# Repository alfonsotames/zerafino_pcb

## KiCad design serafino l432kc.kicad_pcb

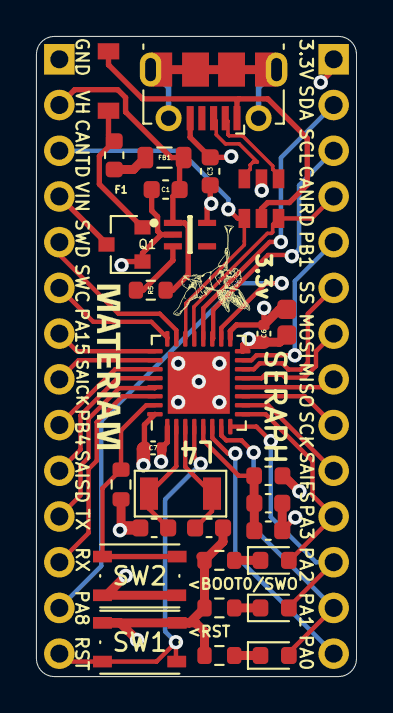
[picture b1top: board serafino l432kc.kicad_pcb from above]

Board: 4 copper layers, 17.8 x 35.6 mm, 31 parts (0 on the bottom side), 41 nets.

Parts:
C1, C10: 1uF; C_0603_1608Metric
C3: 2.2uF; C_0603_1608Metric
C4, C5: 4.3pF; C_0603_1608Metric
C6, C7: 100nF; C_0402_1005Metric
C8: 4.7uF; CP_EIA-1608-08_AVX-J
C9: 10nF; C_0603_1608Metric
D1: RED; LED_0603_1608Metric
D2: B5819W; D_SOD-123
D3: GREEN; LED_0603_1608Metric
D4: BLUE; LED_0603_1608Metric
F1: 200mA; Fuse_0603_1608Metric
FB1: 600@100MHz; L_0805_2012Metric
J1: USB_B_Micro; USB_Micro-B_Molex-105017-0001
J2, J3: Conn_01x14; PinHeader_1x14_P2.54mm_Vertical
L1: 600@100MHz; L_0603_1608Metric
Q1: SI3401A-TP; SOT-23
R1: 270; R_0603_1608Metric
R2: 10K; R_0603_1608Metric
R3: 1K; R_0603_1608Metric
R4: 330; R_0603_1608Metric
R5: 100k; R_0603_1608Metric
SW1, SW2: SW_Push; SW_Push_1P1T_NO_Vertical_Wuerth_434133025816
U1: STLQ020C33R; STMicroelectronics-ESDALC6V1W5-0
U2: USBLC6-2SC6; SOT-23-6
U3: STM32L432KCUx; QFN-32-1EP_5x5mm_P0.5mm_EP3.45x3.45mm
Y1: 32.768K; NX3215SA

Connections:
+3.3VA: C9.1, C10.1, L1.2, U3.5 (VDDA)
+3V3: C3.1, C6.1, C7.1, C8.1, J3.1, L1.1, SW2.2, U1.5 (VOUT), U3.1 (VDD), U3.17 (VDD)
+5V: D2.2 (A), J1.1 (VBUS), U2.5 (VBUS)
+VIN: J2.4, Q1.3 (D)
BOOT0: R2.2, SW2.1, U3.31 (PH3)
CAN_RD: J3.4, U2.6 (I/O1), U3.21 (PA11)
CAN_TD: J2.3, U2.4 (I/O2), U3.22 (PA12)
GND: C1.2, C3.2, C4.2, C5.2, C6.2, C7.2, C8.2, C9.2, C10.2, J1.5 (GND), J2.1, Q1.1 (G), R1.2, R2.1, R3.2, R4.2, SW1.1, U1.2 (GND), U2.2 (GND), U3.16 (VSS), U3.32 (VSS), U3.33 (VSS)
HSE_IN: C4.1, U3.2 (PC14), Y1.1
HSE_OUT: C5.1, U3.3 (PC15), Y1.2
I2C1_SCL: J3.3, U3.19 (PA9)
I2C1_SDA: J3.2, U3.20 (PA10)
NRST: J2.14, SW1.2, U3.4 (NRST)
unnamed: D1.1 (K), R1.1
unnamed: D2.1 (K), F1.2, Q1.2 (S)
unnamed: D3.1 (K), R3.1
unnamed: D4.1 (K), R4.1
unnamed: F1.1, FB1.1
unnamed: R5.2, U1.3 (EN)
PA0: J3.14, U3.6 (PA0)
PA1: D1.2 (A), J3.13, U3.7 (PA1)
PA2: D3.2 (A), J3.12, U3.8 (PA2)
PA3: D4.2 (A), J3.11, U3.9 (PA3)
PA8: J2.13, U3.18 (PA8)
PA15: J2.7, U3.25 (PA15)
PB1: J3.5, U3.15 (PB1)
PB4: J2.9, U3.27 (PB4)
SAI1_FS_B: J3.10, U3.10 (PA4)
SAI1_SCK_B: J2.8, U3.26 (PB3)
SAI1_SD_B: J2.10, U3.28 (PB5)
SPI1_MISO: J3.8, U3.12 (PA6)
SPI1_MOSI: J3.7, U3.13 (PA7)
SPI1_SCK: J3.9, U3.11 (PA5)
SPI1_SS: J3.6, U3.14 (PB0)
SWCLK: J2.6, U3.24 (PA14)
SWDIO: J2.5, U3.23 (PA13)
USART1_RX: J2.12, U3.30 (PB7)
USART1_TX: J2.11, U3.29 (PB6)
USB_CONN_D+: J1.3 (D+), U2.3 (I/O2)
USB_CONN_D-: J1.2 (D-), U2.1 (I/O1)
VHIGH: C1.1, FB1.2, J2.2, R5.1, U1.1 (VIN)

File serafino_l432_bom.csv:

Reference, Quantity, Value, Footprint, Datasheet, Part No.
C1 C10 ,2,"1uF","Capacitor_SMD:C_0603_1608Metric","~","0603DC105KAT2A "
C3 ,1,"2.2uF","Capacitor_SMD:C_0603_1608Metric","~","C1608X7R1A225K080AE "
C4 C5 ,2,"4.3pF","Capacitor_SMD:C_0603_1608Metric","~","VJ0603D4R3BXPAJ"
C6 C7 ,2,"100nF","Capacitor_SMD:C_0402_1005Metric","~","EMF105B7104MVHF "
C8 ,1,"4.7uF","Capacitor_Tantalum_SMD:CP_EIA-1608-08_AVX-J","~","F980J475MMA"
C9 ,1,"10nF","Capacitor_SMD:C_0603_1608Metric","~","C0603X103K5RAC3316 "
D1 ,1,"RED","LED_SMD:LED_0603_1608Metric","~","155060RS75300"
D2 ,1,"B5819W","Diode_SMD:D_SOD-123","~","B5819W-TP "
D3 ,1,"GREEN","LED_SMD:LED_0603_1608Metric","~","155060GS75300"
D4 ,1,"BLUE","LED_SMD:LED_0603_1608Metric","~","155060BS75300"
F1 ,1,"500mA","Fuse:Fuse_1206_3216Metric","~","1206L025YR"
FB1 ,1,"600@100MHz","Inductor_SMD:L_0805_2012Metric","~","HZ0805E601R-10 "
J1 ,1,"USB_B_Micro","Connector_USB:USB_Micro-B_Molex-105017-0001","~","105017-0001 "
J2 J3 ,2,"Conn_01x14","Connector_PinHeader_2.54mm:PinHeader_1x14_P2.54mm_Vertical","~"
L1 ,1,"600@100MHz","Inductor_SMD:L_0603_1608Metric","~","BLM18AG601SN1D "
Q1 ,1,"SI3401A-TP","Package_TO_SOT_SMD:SOT-23","https://www.mouser.mx/datasheet/2/258/SI3401A(SOT-23)-V1-162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","SI3401A-TP"
R1 R3 R4 ,3,"1K","Resistor_SMD:R_0603_1608Metric","~","RC0603FR-071KL"
R2 ,1,"10K","Resistor_SMD:R_0603_1608Metric","~","RC0603FR-0710KL"
R5 ,1,"100k","Resistor_SMD:R_0603_1608Metric","~","RC0603FR-07100KL"
SW1 SW2 ,2,"SW_Push","Button_Switch_SMD:SW_Push_1P1T_NO_Vertical_Wuerth_434133025816","~","434133025816 "
U1 ,1,"AP2112K-3.3","Package_TO_SOT_SMD:SOT-23-5","https://www.diodes.com/assets/Datasheets/AP2112.pdf","AP2112K-3.3TRG1"
U2 ,1,"USBLC6-2SC6","Package_TO_SOT_SMD:SOT-23-6","https://www.st.com/resource/en/datasheet/usblc6-2.pdf","USBLC6-2SC6"
U3 ,1,"STM32L432KCUx","Package_DFN_QFN:QFN-32-1EP_5x5mm_P0.5mm_EP3.45x3.45mm","http://www.st.com/st-web-ui/static/active/en/resource/techni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","STM32L432KCU6"
Y1 ,1,"32.768K","serafino l432kc:NX3215SA","~","NX3215SA-32.768KHZ-EXS00A-MU00525"

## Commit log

2020-12-02 Avances
2020-12-03 Working on the power supply
2020-12-04 Add MP2359DJ Buck Converter to Serafino Lib
2020-12-05 avances...
2020-12-07 Cambio de Power Supply
2020-12-07 Updated pins
2020-12-08 Upgrade to high effiency buck converter
2020-12-08 Battery charger
2020-12-08 Simplificacion del Power Supply y eliminación del battery charger
2020-12-09 Pinout definition
2020-12-09 PCB layout
2020-12-09 Layout..
2020-12-10 More layouts...
2020-12-10 Layout avanzado...
2020-12-10 Added 3D models...
2020-12-11 PCB Polish
2020-12-12 Starting to route...
2020-12-12 more layoutss...
2020-12-13 started with differential tracks
2020-12-14 Nuevo layout
2020-12-15 new layout
2020-12-15 removed user button
2020-12-16 Tracks...
2020-12-16 more tracks
2020-12-16 almost finished tracks, 5v is a problem
2020-12-17 Silk screen
2020-12-17 completed tracks
2021-01-07 Cambio de layout en leds
2021-01-09 BOM start
2021-01-29 version acorde con primer prototipo
2021-01-29 My name is Seraph
2021-01-29 Rework for pwn leds
2021-01-30 PWM Leds
2021-02-02 BOOT0 a SW0
2021-02-02 Silk screen updated
2021-02-02 DFU LED Indicator (PA6/MISO)
2021-02-03 Finished back labels
2021-02-04 Adjusted LED resistor values, changed BOOT0 to PA0 in silk screen.
2021-02-11 Led Specs
2021-02-24 Disconnected LED2 from MISO since PA2 (LED1) is already on in DFU mode
2021-02-26 Seraph L4 v1.0
2021-03-03 USB placement correction
2021-03-16 ajustes
2021-04-13 Change LDO
2021-04-17 Updated power supply
2022-04-16 Changed Fuse to 200ma in accordance to the power supply capacity
